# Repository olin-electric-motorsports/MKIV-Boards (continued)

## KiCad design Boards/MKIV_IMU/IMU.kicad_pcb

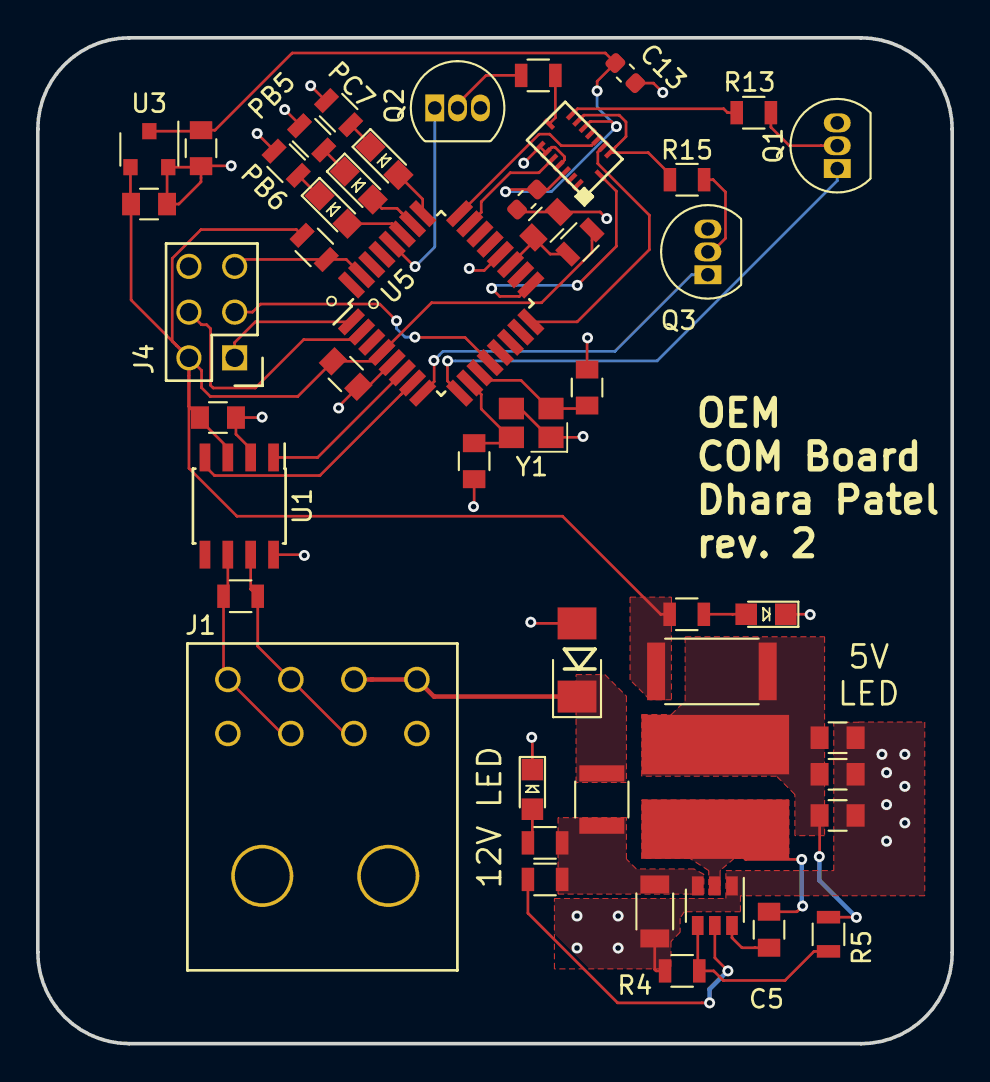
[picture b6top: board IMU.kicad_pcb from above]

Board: 2 copper layers, 50.8 x 55.9 mm, 48 parts (0 on the bottom side), 42 nets.

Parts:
C1, C4, C5, C9, C10, C12: C_0.1uF; C_0805_OEM
C2: C_100pF; C_0805_OEM
C3: C_22uF; C_1206_OEM
C6, C8: C_30pF; C_0805_OEM
C7: C_47uF; C_0805_OEM
C11: C_1uF; C_0805_OEM
C13, C14: C_100nF; C_0603_1608Metric
D1, D2, D3, D4, D5: LED_0805; LED_0805_OEM
D7: D_Zener_18V; DO-214AA
F1: 500mA; Fuse_1210
J1: UF_8_RA; Ultrafit_8_RA
J4: CONN_02X03; Pin_Header_Straight_2x03
L1: L_4.7uH; 4.7uH_Inductor_OEM
PB5, PB6: R_200; R_0805_OEM
PC7: R_200; R_0805_OEM
Q1, Q2, Q3: 2N7000; TO-92_Inline
R1: R_100; R_0805_OEM
R2: R_1k; R_0805_OEM
R3, R4, R8: R_10k; R_0805_OEM
R5: R_51.1k; R_0805_OEM
R7: R_120; R_0805_OEM
R9: R_0_Jumper; R_2512_OEM
R12: R_200; R_0805_OEM
R13, R14, R15: R_10K; R_0805_OEM
U1: CAN_Transceiver; SOIC-8_3.9x4.9mm_Pitch1.27mm_OEM
U2: TPS561201; SOT-23-6_OEM
U3: LM3480; SOT-23-3_OEM
U4: BMI088; bmi088
U5: ATMEGA16M1; TQFP-32_7x7mm_Pitch0.8mm
Y1: Crystal_SMD; Crystal_SMD_FA238

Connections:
/3.3V: C10.1, C13.2, C14.1, U3.1, U4.3, U4.11
/12V: D7.1, F1.1, J1.3, J1.7
/12V_Fused: C3.1, F1.2, R2.1, R3.1, U2.3
/CANH: J1.2, J1.6, R7.1, U1.7
/CANL: J1.1, J1.5, R7.2, U1.6
/CS_ACCEL: U4.14, U5.16
/CS_GYRO: U4.5, U5.23
/INT1: U4.16, U5.17
/INT4: U4.13, U5.24
/MISO: J4.1, U5.1
/MISO2: Q3.1, U5.8
/MOSI: J4.4, U5.2
/MOSI2: Q1.1, U5.9
/PLED1: D3.2, U5.25
/PLED2: D4.2, U5.26
/PLED3: D5.2, U5.27
/RESET: J4.5, R8.2, U5.31
/RXCAN: U1.4, U5.7
/SCK: J4.3, U5.12
/SCK2: Q2.1, U5.28
/TXCAN: U1.1, U5.6
GND: C1.2, C2.2, C3.2, C4.2, C6.2, C7.2, C8.2, C9.2, C10.2, C11.2, C12.2, C13.1, C14.2, D1.1, D2.1, D7.2, J1.4, J1.8, J4.6, PB5.2, PB6.2, PC7.2, Q1.3, Q2.3, Q3.3, R4.2, U1.2, U1.8, U2.1, U3.3, U4.4, U4.6, U4.7, U5.5, U5.20, Y1.2, Y1.4
unnamed: C2.1, R1.2, U5.19
unnamed: C5.1, U2.6
unnamed: C5.2, L1.1, U2.2
unnamed: C6.1, U5.11, Y1.1
unnamed: C8.1, U5.10, Y1.3
unnamed: C7.1, C11.1, C12.1, L1.2, R5.2, R9.2
unnamed: D1.2, R2.2
unnamed: D2.2, R12.2
unnamed: D3.1, PC7.1
unnamed: D4.1, PB5.1
unnamed: D5.1, PB6.1
unnamed: Q1.2, R13.1
unnamed: Q2.2, R14.1
unnamed: Q3.2, R15.2
unnamed: R3.2, U2.5
unnamed: R4.1, R5.1, U2.4
unnamed: R13.2, U4.9
unnamed: R14.2, U4.8
unnamed: R15.1, U4.10, U4.15
VCC: C1.1, C4.1, C9.1, J4.2, R1.1, R8.1, R9.1, R12.1, U1.3, U3.2, U5.4

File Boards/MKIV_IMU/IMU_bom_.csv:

Component,Description,Part,References,Value,Footprint,Quantity Per PCB,Datasheet,Package,MPN,MFN,PurchasingLink,Purchasing Link
1,"Capacitor, 0.1uF, 50V, 5%, 0805",C_0.1uF,C1 C4 C5 C9 C10 C12,C_0.1uF,C_0805_OEM,6,http://datasheets.avx.com/X7RDielectric.pdf,Value,478-3352-1-ND,Digi-Key DK,https://www.digikey.com/products/en?keywords=478-3352-1-ND,
2,"Capacitor, 0.1uF, 25V, 10%, 0603",C_100nF,C13 C14,C_100nF,C_0603_1608Metric,2,http://www.samsungsem.com/kr/support/product-search/mlcc/CL1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,,1276-6717-1-ND,DK,https://www.digikey.com/product-detail/en/samsung-electro-me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,
3,"Capacitor, 100pF, 50V, 5%, 0805",C_100pF,C2,C_100pF,C_0805_OEM,1,https://content.kemet.com/datasheets/KEM_C1003_C0G_SMD.pdf,Value,399-1122-1-ND,Digi-Key,https://www.digikey.com/product-detail/en/kemet/C0805C101J5G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,
4,"Capacitor, 1uF, 25V, 10%, 0805",C_1uF,C11,C_1uF,C_0805_OEM,1,http://datasheets.avx.com/X7RDielectric.pdf,Value,478-10487-1-ND,Digi-Key,https://www.digikey.com/product-detail/en/avx-corporation/08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,
5,"Capacitor, 22uF, 16V, 20%, 1206",C_22uF,C3,C_22uF,C_1206_OEM,1,http://www.samsungsem.com/kr/support/product-search/mlcc/__i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,Value,1276-2725-1-ND,Digi-Key,https://www.digikey.com/products/en?keywords=1276-2725-1-ND,
6,"Capacitor, 30pF, 50V, 5%, 0805",C_30pF,C6 C8,C_30pF,C_0805_OEM,2,https://media.digikey.com/pdf/Data%20Sheets/Samsung%20PDFs/C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,Value,1276-1130-1-ND,Digi-Key,https://www.digikey.com/product-detail/en/samsung-electro-me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,
7,"Capacitor, 47uF, 6.3V, 20%, 0805",C_47uF,C7,C_47uF,C_0805_OEM,1,http://www.yuden.co.jp/productdata/catalog/en/mlcc_all_e.pdf,Value,587-4280-1-ND,Digi-Key,https://www.digikey.com/product-detail/en/taiyo-yuden/JMK212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,
8,"Diode, Zener, 18V, 5W, 5%",D_Zener_18V,D7,D_Zener_18V,DO-214AA,1,http://www.mccsemi.com/up_pdf/SMBJ5338B-SMBJ5388B(SMB).pdf,DO-214AA (SMB),SMBJ5355B-TPMSCT-ND,Digi-Key,https://www.digikey.com/products/en?keywords=SMBJ5355B-TPMSCT-ND,
9,"LED, Green, 2.2V, 20mA, 0805",LED_0805,D1 D2 D3 D4 D5,LED_0805,LED_0805_OEM,5,http://www.osram-os.com/Graphics/XPic9/00078860_0.pdf,Value,475-1410-1-ND,Digi-Key DK,https://www.digikey.com/products/en?keywords=475-1410-1-ND,
10,"Fuse, PTC, 500mA, 16V, 1210",F_500mA_16V,F1,500mA,Fuse_1210,1,https://belfuse.com/resources/CircuitProtection/datasheets/0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,Value,507-1786-1-ND,Digi-Key,https://www.digikey.com/product-detail/en/bel-fuse-inc/0ZCH0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,
11,"Connector header through hole 2x3 0.100"" (2.54mm)",CONN_02X03,J4,CONN_02X03,Pin_Header_Straight_2x03,1,http://portal.fciconnect.com/Comergent//fci/drawing/67996.pdf,Value,609-3234-ND,Digi-Key,https://www.digikey.com/product-detail/en/amphenol-fci/67997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,
12,Micro-MaTch connector 8 pin female right angle,UF_8_RA,J1,UF_8_RA,Ultrafit_8_RA,1,https://www.molex.com/pdm_docs/sd/1723161306_sd.pdf,,WM11861-ND,DigiKey,https://www.digikey.com/product-detail/en/molex/1723161308/W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,
13,"Inductor, 4.7uH, 4.4A, 25mOhm, 20%",L_4.7uH,L1,L_4.7uH,4.7uH_Inductor_OEM,1,https://product.tdk.com/info/en/documents/wdcatalog/withdraw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,Value,445-6583-1-ND,Digi-Key,https://www.digikey.com/product-detail/en/tdk-corporation/VL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,
14,"Resistor, 0 ohm jumper, 0.1W, 0603",R_0,R9,R_0_Jumper,R_2512_OEM,1,http://www.te.com/commerce/DocumentDelivery/DDEController?Ac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,Value,A121322CT-ND,Digi-Key,https://www.digikey.com/products/en?keywords=A121322CT-ND,
15,"Resistor, 100, 0.25W, 1%, 0805",R_100,R1,R_100,R_0805_OEM,1,https://www.seielect.com/Catalog/SEI-rncp.pdf,Value,RNCP0805FTD100RCT-ND,Digi-Key,https://www.digikey.com/products/en?keywords=RNCP0805FTD100RCT-ND,
16,"Resistor, 10K, 5W, 1%, Axial",R_10K_HV,R3 R4,R_10k,R_0805_OEM,2,http://www.bourns.com/data/global/pdfs/CRS.pdf,Value,CRS0805-FX-1002ELFCT-ND,Digi-Key,https://www.digikey.com/products/en?keywords=CRS0805-FX-1002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,
17,"Resistor, 10K, 0.25W, 1%, 0805",R_10K,R8,R_10k,R_0805_OEM,1,http://www.bourns.com/data/global/pdfs/CRS.pdf,Value,CRS0805-FX-1002ELFCT-ND,Digi-Key,https://www.digikey.com/products/en?keywords=CRS0805-FX-1002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,
18,"Resistor, 120, 0.125W, 1%, 0805",R_120,R7,R_120,R_0805_OEM,1,https://www.mouser.com/datasheet/2/315/AOA0000C304-1149620.pdf,,667-ERJ-6ENF1200V,DK,https://www.mouser.com/ProductDetail/Panasonic-Industrial-De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,
19,"Resistor, 1K, 0.25W, 1%, 0805",R_1K,R2,R_1k,R_0805_OEM,1,https://www.seielect.com/Catalog/SEI-rncp.pdf,Value,RNCP0805FTD1K00CT-ND,Digi-Key,https://www.digikey.com/products/en?keywords=RNCP0805FTD1K00CT-ND,
20,"Resistor, 200, 0.125W, 5%, 0805",R_200,R6 R10 R11 R12,R_200,R_0805_OEM,4,https://www.seielect.com/Catalog/SEI-RMCF_RMCP.pdf,Value,RMCF0805JT200RCT-ND,DK Digi-Key,https://www.digikey.com/products/en?keywords=RMCF0805JT200RCT-ND,
21,"Resistor, 51.1K, 0.125W, 1%, 0805",R_51.1K,R5,R_51.1k,R_0805_OEM,1,http://www.yageo.com.tw/exep/pages/download/literatures/PYu-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,Value,311-51.1KCRCT-ND,Digi-Key,https://www.digikey.com/products/en?keywords=311-51.1KCRCT-ND,
22,"Microcontroller, 8-bit, 1KB RAM, 16KB Flash",ATMEGA16M1,U5,ATMEGA16M1,TQFP-32_7x7mm_Pitch0.8mm,1,http://ww1.microchip.com/downloads/en/DeviceDoc/Atmel-8209-8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,,ATMEGA16M1-AU-ND,DK,https://www.digikey.com/product-detail/en/atmel/ATMEGA16M1-A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,
23,,BMI088,U4,BMI088,bmi088,1,https://ae-bst.resource.bosch.com/media/_tech/media/product_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,,,,,https://www.digikey.com/product-detail/en/bosch-sensortec/BM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
24,"High speed CAN transceiver, 1Mb/s",MCP2561-E_SN,U1,CAN_Transceiver,SOIC-8_3.9x4.9mm_Pitch1.27mm_OEM,1,http://www.microchip.com/mymicrochip/filehandler.aspx?ddocna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,Value,MCP2561-E/SN-ND,Digi-Key,https://www.digikey.com/products/en?keywords=mcp2561-e%2Fsn,
25,"Linear regulator, 30V max input, 3.3V output, 100mA",LM3480,U3,LM3480,SOT-23-3_OEM,1,http://www.ti.com/lit/ds/symlink/lm3480.pdf,,LM3480IM3-3.3CT-ND,DK,https://www.digikey.com/product-detail/en/texas-instruments/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,
26,"Buck converter, 4.5-17V input, adj 0.76-7V output, 1A, 580kHz",TPS561201,U2,TPS561201,SOT-23-6_OEM,1,http://www.ti.com/lit/ds/symlink/tps561201.pdf,Value,TPS561201,Digi-Key,https://www.digikey.com/products/en?keywords=296-46928-1-ND,
27,CRYSTAL 16.0000MHZ 18PF SMD,Crystal_SMD,Y1,Crystal_SMD,Crystal_SMD_FA238,1,https://support.epson.biz/td/api/doc_check.php?dl=brief_FA-2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,Value,SER3686CT-ND,Digi-Key,https://www.digikey.com/products/en?keywords=SER3686CT-ND,
,,,,,,,,,,,,
,,,,,,,,,,,,
,,,,,,,,,,,,
,,,,,,,,,,,,
,,,,,,,,,,,,
Component Groups:,27,,,,,,,,,,,
Component Count:,42,,,,,,,,,,,
Fitted Components:,42,,,,,,,,,,,
Number of PCBs:,1,,,,,,,,,,,
Total components:,42,,,,,,,,,,,
Schematic Version:,,,,,,,,,,,,
Schematic Date:,,,,,,,,,,,,
BoM Date:,Tue 12 Feb 2019 12:32:12 AM EST,,,,,,,,,,,
Schematic Source:,/home/dpatel1/Documents/Formula/MKIV-Boards/Boards/MKIV_IMU/IMU.sch,,,,,,,,,,,
KiCad Version:,Eeschema 5.0.1-33cea8e~68~ubuntu18.04.1,,,,,,,,,,,
